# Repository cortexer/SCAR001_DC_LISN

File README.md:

# SCAR001_DC_LISN
5µH DC LISN for conducted EMI measurements

This is a simple 5µH DC LISN design made in KiCad.
A "Line Impedance Stabilization Network" (LISN) is used for conducted EMC measurements.
It is a partial implementation of Linear Technology's DC2130A.
It features a -10dB attenuator and provides AC coupling to the spectrum analyzer using 50 ohm transmission lines
through an SMA connector.

It is a very simple design. For some more information look at the schematic.

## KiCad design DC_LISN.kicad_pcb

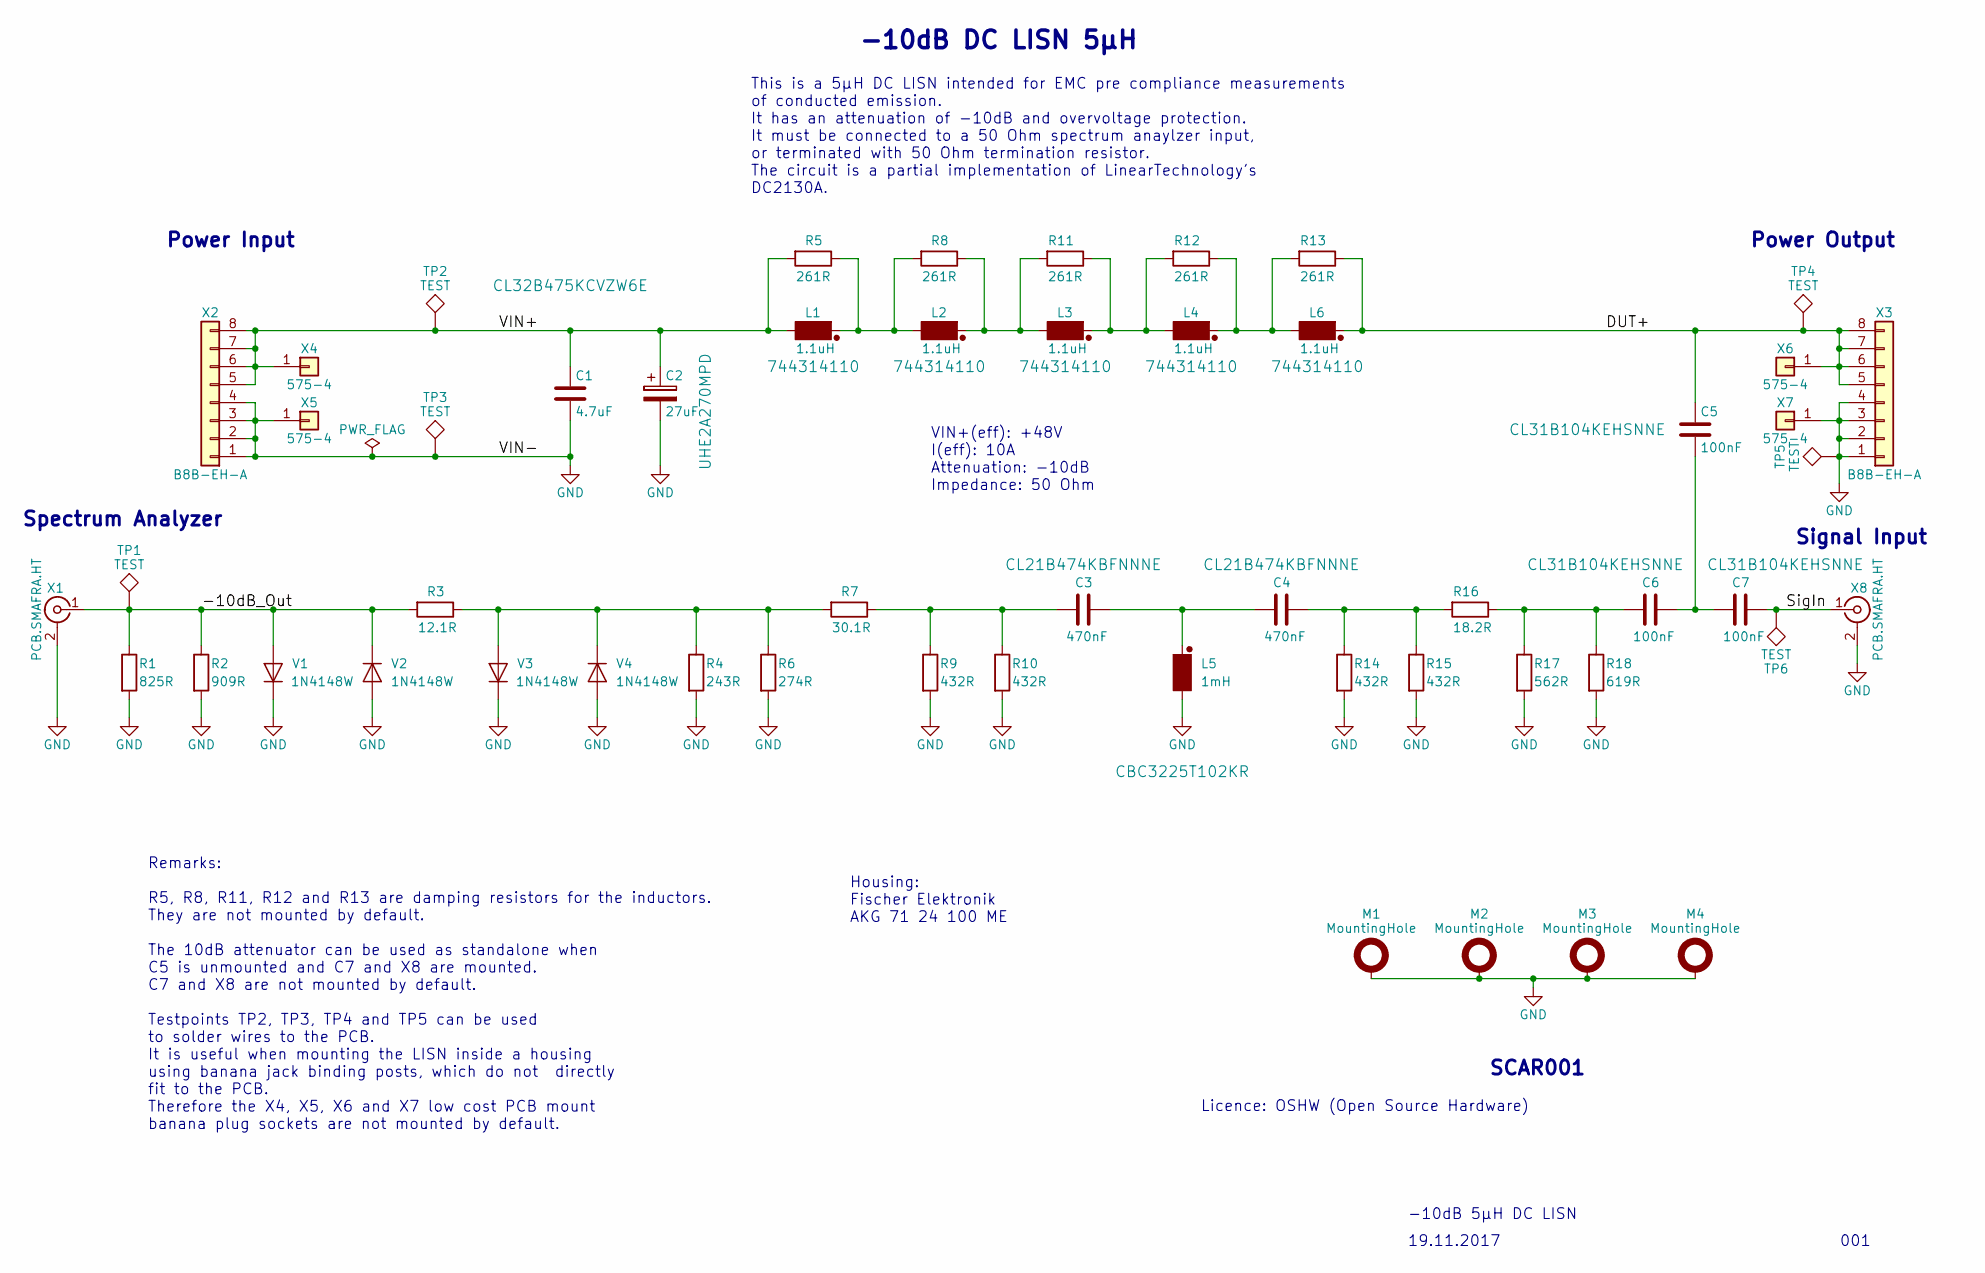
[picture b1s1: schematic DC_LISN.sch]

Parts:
C1: 4.7uF; C_1210
C2: 27uF; C_Alu_Radial_D8.0mm_P3.50mm
C3, C4: 470nF; C_0805
C5, C6, C7: 100nF; C_1206
L1, L2, L3, L4, L6: 1.1uH; L_Wuerth_744314110
L5: 1mH; L_1210
M1, M2, M3, M4: MountingHole; M_MountingHole_3.5mm_Pad_Via
R1: 825R; R_0603
R2: 909R; R_0603
R3: 12.1R; R_0603
R4: 243R; R_0603
R5, R8, R11, R12, R13: 261R; R_0603
R6: 274R; R_0603
R7: 30.1R; R_0603
R9, R10, R14, R15: 432R; R_0603
R16: 18.2R; R_0603
R17: 562R; R_0603
R18: 619R; R_0603
TP1, TP6: TEST; TP_1mm
TP2, TP3, TP4, TP5: TEST; TP_MillMax_2501
V1, V2, V3, V4: 1N4148W; V_SOD-123
X1, X8: PCB.SMAFRA.HT; X_SMA_THT_Jack_Straight_PCB.SMAFRA.HT
X2, X3: B8B-EH-A; X_JST_EH_B08B-EH-A_08x2.50mm_Straight
X4, X5, X6, X7: 575-4; X_Keystone_575-4

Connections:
/-10dB_Out: R1.1, R2.1, R3.2, TP1.1, V1.2 (A), V2.1 (K), X1.1 (In)
/DUT+: C5.1, L6.1, R13.1, TP4.1, X3.5, X3.6, X3.7, X3.8, X6.1
/SigIn: C7.1, TP6.1, X8.1 (In)
/VIN+: C1.1, C2.1, L1.2, R5.2, TP2.1, X2.5, X2.6, X2.7, X2.8, X4.1
GND: C1.2, C2.2, L5.2, M1.1, M2.1, M3.1, M4.1, R1.2, R2.2, R4.2, R6.2, R9.2, R10.2, R14.2, R15.2, R17.2, R18.2, TP3.1, TP5.1, V1.1 (K), V2.2 (A), V3.1 (K), V4.2 (A), X1.2 (Ext), X2.1, X2.2, X2.3, X2.4, X3.1, X3.2, X3.3, X3.4, X5.1, X7.1, X8.2 (Ext)
unnamed: C3.1, C4.2, L5.1
unnamed: C3.2, R7.1, R9.1, R10.1
unnamed: C4.1, R14.1, R15.1, R16.2
unnamed: C5.2, C6.1, C7.2
unnamed: C6.2, R16.1, R17.1, R18.1
unnamed: L1.1, L2.2, R5.1, R8.2
unnamed: L2.1, L3.2, R8.1, R11.2
unnamed: L3.1, L4.2, R11.1, R12.2
unnamed: L4.1, L6.2, R12.1, R13.2
unnamed: R3.1, R4.1, R6.1, R7.2, V3.2 (A), V4.1 (K)

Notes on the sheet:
-10dB DC LISN 5µH
This is a 5µH DC LISN intended for EMC pre compliance measurements of conducted emission. It has an attenuation of -10dB and overvoltage protection. It must be connected to a 50 Ohm spectrum anaylzer input, or terminated with 50 Ohm termination resistor. The circuit is a partial implementation of L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
VIN+(eff): +48V I(eff): 10A Attenuation: -10dB Impedance: 50 Ohm
19.11.2017
001
-10dB 5µH DC LISN
Licence: OSHW (Open Source Hardware)
Power Input
Spectrum Analyzer
Power Output
Housing: Fischer Elektronik AKG 71 24 100 ME
SCAR001
Remarks: R5, R8, R11, R12 and R13 are damping resistors for the inductors. They are not mounted by default. The 10dB attenuator can be used as standalone when C5 is unmounted and C7 and X8 are mounted. C7 and X8 are not mounted by default. Testpoints TP2, TP3, TP4 and TP5 can be used to solder wire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
Signal Input

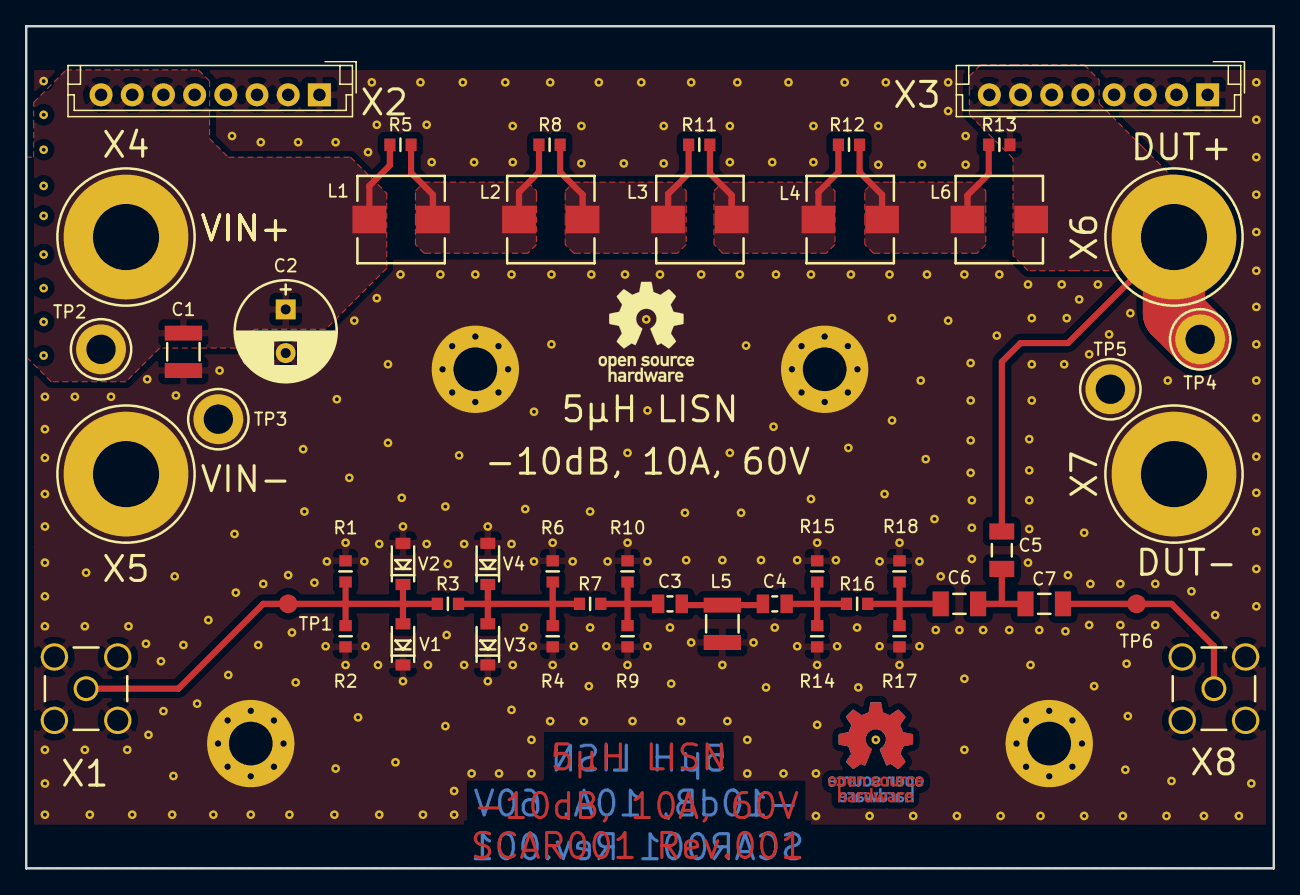
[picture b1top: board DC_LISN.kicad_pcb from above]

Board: 4 copper layers, 100.0 x 67.5 mm, 53 parts (0 on the bottom side), 15 nets.

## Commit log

2017-12-02 Schematic and Layout: Added initial schematic and layout. This is a 5µH DC LISN to be used for conducted EMI measurements.
2017-12-03 Licensing: Changed to OSHW Changed licensing to open source hardware. Added an additional signal input for use as standalone attenuator.
2017-12-03 Schematic: Added comments
2017-12-03 Schematic: Improved comments
2017-12-03 Layout: Documented Stackup and Impedances
2017-12-03 Gerber: Generated fabrication data. Also printed schematic and updated BOM.
2017-12-05 Created ReadMe File
    Added new ReadMe file which will be shown on Github per default.
2017-12-26 Schematic: Comments updated Added binding post order numbers to comments.
2017-12-26 Simulations: Created Simulations Created two LTspice simulations: - Impedance as seen from DUT. - Transfer function from DUT to spectrum analyzer.
2017-12-26 Screenshots: Added Screenshots Added screenshots for layout from top and 3D view.
2017-12-28 Measurements: Transfer Function Added measurements of transfer function, from DUT terminals to -10dB output.
2017-12-30 Images: Added Image Added images of final LISN and raw PCB.
